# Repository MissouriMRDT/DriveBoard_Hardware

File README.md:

# DriveBoard_Hardware
Hardware files for Drive Board

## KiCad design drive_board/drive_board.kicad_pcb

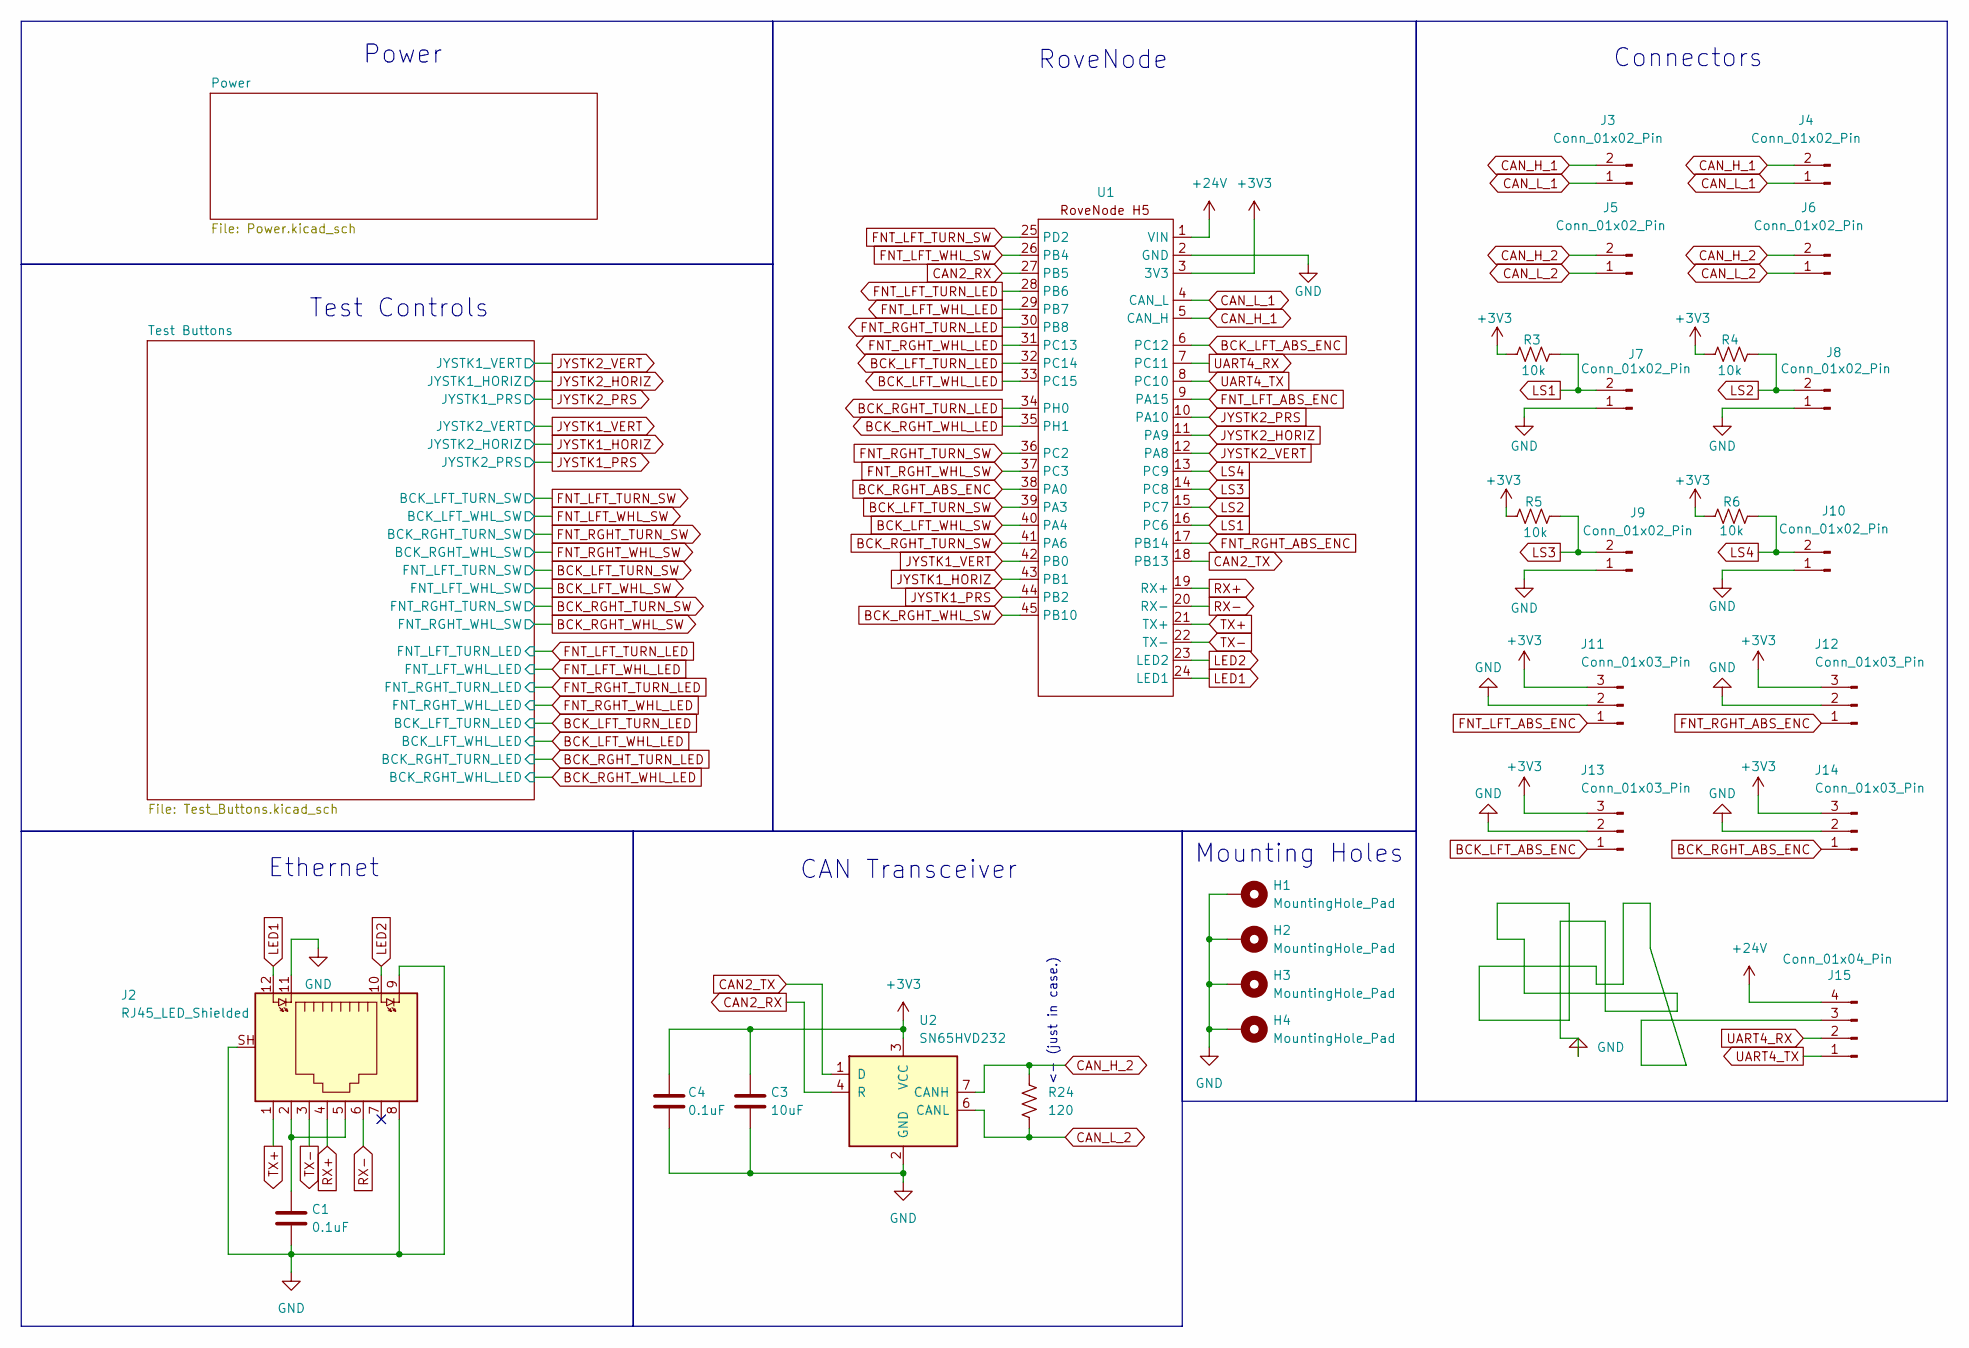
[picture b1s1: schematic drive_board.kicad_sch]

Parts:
C1, C4: 0.1uF; C_0603_1608Metric_Pad1.08x0.95mm_HandSolder
C3: 10uF; C_0603_1608Metric_Pad1.08x0.95mm_HandSolder
H1, H2, H3, H4: MountingHole_Pad; 4_40_Hole_Pad_Via
J2: RJ45_LED_Shielded; RJ45_Teensy
J3, J4, J5, J6, J7, J8, J9, J10: Conn_01x02_Pin; JST_PH_B2B-PH-K_1x02_P2.00mm_Vertical
J11, J12, J13, J14: Conn_01x03_Pin; JST_PH_B3B-PH-K_1x03_P2.00mm_Vertical
J15: Conn_01x04_Pin; JST_PH_B4B-PH-K_1x04_P2.00mm_Vertical
R3, R4, R5, R6: 10k; R_0603_1608Metric_Pad0.98x0.95mm_HandSolder
R24: 120; R_0603_1608Metric_Pad0.98x0.95mm_HandSolder
U1: RoveNode_H5
U2: SN65HVD232; SOIC-8_3.9x4.9mm_P1.27mm

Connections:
+3V3: C3.1, C4.1, J11.3, J12.3, J13.3, J14.3, R3.1, R4.1, R5.1, R6.1, U1.3 (3V3), U2.3 (VCC); also elsewhere on the board
+24V: J15.4, U1.1 (VIN); also elsewhere on the board
BCK_LFT_ABS_ENC: J13.1, U1.6 (PC12)
BCK_LFT_TURN_LED: U1.32 (PC14); also elsewhere on the board
BCK_LFT_TURN_SW: U1.39 (PA3); also elsewhere on the board
BCK_LFT_WHL_LED: U1.33 (PC15); also elsewhere on the board
BCK_LFT_WHL_SW: U1.40 (PA4); also elsewhere on the board
BCK_RGHT_ABS_ENC: J14.1, U1.38 (PA0)
BCK_RGHT_TURN_LED: U1.34 (PH0); also elsewhere on the board
BCK_RGHT_TURN_SW: U1.41 (PA6); also elsewhere on the board
BCK_RGHT_WHL_LED: U1.35 (PH1); also elsewhere on the board
BCK_RGHT_WHL_SW: U1.45 (PB10); also elsewhere on the board
CAN2_RX: U1.27 (PB5), U2.4 (R)
CAN2_TX: U1.18 (PB13), U2.1 (D)
CAN_H_1: J3.2, J4.2, U1.5 (CAN_H)
CAN_H_2: J5.2, J6.2, R24.1, U2.7 (CANH)
CAN_L_1: J3.1, J4.1, U1.4 (CAN_L)
CAN_L_2: J5.1, J6.1, R24.2, U2.6 (CANL)
FNT_LFT_ABS_ENC: J11.1, U1.9 (PA15)
FNT_LFT_TURN_LED: U1.28 (PB6); also elsewhere on the board
FNT_LFT_TURN_SW: U1.25 (PD2); also elsewhere on the board
FNT_LFT_WHL_LED: U1.29 (PB7); also elsewhere on the board
FNT_LFT_WHL_SW: U1.26 (PB4); also elsewhere on the board
FNT_RGHT_ABS_ENC: J12.1, U1.17 (PB14)
FNT_RGHT_TURN_LED: U1.30 (PB8); also elsewhere on the board
FNT_RGHT_TURN_SW: U1.36 (PC2); also elsewhere on the board
FNT_RGHT_WHL_LED: U1.31 (PC13); also elsewhere on the board
FNT_RGHT_WHL_SW: U1.37 (PC3); also elsewhere on the board
GND: C1.2, C3.2, C4.2, H1.1 (1_1), H2.1 (1_1), H3.1 (1_1), H4.1 (1_1), J2.8, J2.9, J2.11, J2.SH, J7.1, J8.1, J9.1, J10.1, J11.2, J12.2, J13.2, J14.2, J15.3, U1.2 (GND), U2.2 (GND); also elsewhere on the board
JYSTK1_HORIZ: U1.43 (PB1); also elsewhere on the board
JYSTK1_PRS: U1.44 (PB2); also elsewhere on the board
JYSTK1_VERT: U1.42 (PB0); also elsewhere on the board
JYSTK2_HORIZ: U1.11 (PA9); also elsewhere on the board
JYSTK2_PRS: U1.10 (PA10); also elsewhere on the board
JYSTK2_VERT: U1.12 (PA8); also elsewhere on the board
LED1: J2.12, U1.24 (LED1)
LED2: J2.10, U1.23 (LED2)
LS1: J7.2, R3.2, U1.16 (PC6)
LS2: J8.2, R4.2, U1.15 (PC7)
LS3: J9.2, R5.2, U1.14 (PC8)
LS4: J10.2, R6.2, U1.13 (PC9)
unnamed: C1.1, J2.2, J2.5
RX+: J2.4, U1.19 (RX+)
RX-: J2.6, U1.20 (RX-)
TX+: J2.1, U1.21 (TX+)
TX-: J2.3, U1.22 (TX-)
UART4_RX: J15.2, U1.7 (PC11)
UART4_TX: J15.1, U1.8 (PC10)

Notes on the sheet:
Power
Test Controls
Ethernet
Connectors
CAN Transceiver
<- (just in case.)
RoveNode
Mounting Holes

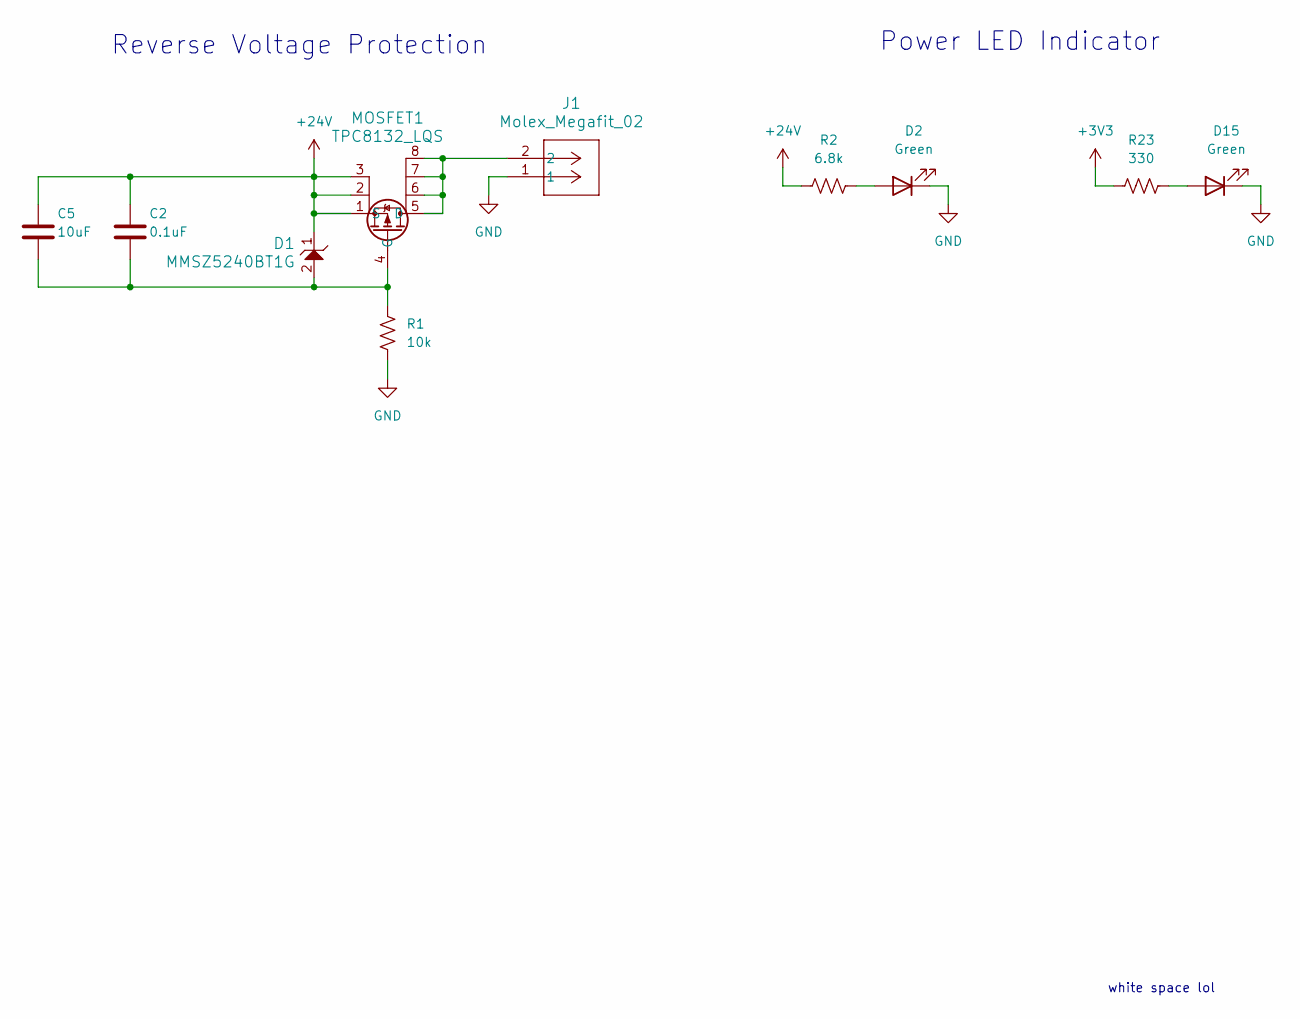
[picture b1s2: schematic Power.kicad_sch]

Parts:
C2: 0.1uF; C_0603_1608Metric_Pad1.08x0.95mm_HandSolder
C5: 10uF; C_0603_1608Metric_Pad1.08x0.95mm_HandSolder
D1: MMSZ5240BT1G; SOD-123_ONS-L
D2, D15: Green; LED_0603_1608Metric_Pad1.05x0.95mm_HandSolder
J1: Molex_Megafit_02; MOLEX_MegaFit_02_Vertical
MOSFET1: TPC8132_LQS; SOIC-8_3.9x4.9mm_P1.27mm
R1: 10k; R_0603_1608Metric_Pad0.98x0.95mm_HandSolder
R2: 6.8k; R_0603_1608Metric_Pad0.98x0.95mm_HandSolder
R23: 330; R_0603_1608Metric_Pad0.98x0.95mm_HandSolder

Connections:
+3V3: R23.1; also elsewhere on the board
+24V: C2.1, C5.1, D1.1, MOSFET1.1 (S), MOSFET1.2, MOSFET1.3, R2.1; also elsewhere on the board
GND: D2.1 (K), D15.1 (K), J1.1, R1.2; also elsewhere on the board
unnamed: D2.2 (A), R2.2
unnamed: D15.2 (A), R23.2
unnamed: J1.2, MOSFET1.5 (D), MOSFET1.6, MOSFET1.7, MOSFET1.8
unnamed: C2.2, C5.2, D1.2, MOSFET1.4 (G), R1.1

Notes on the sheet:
white space lol
Reverse Voltage Protection
Power LED Indicator

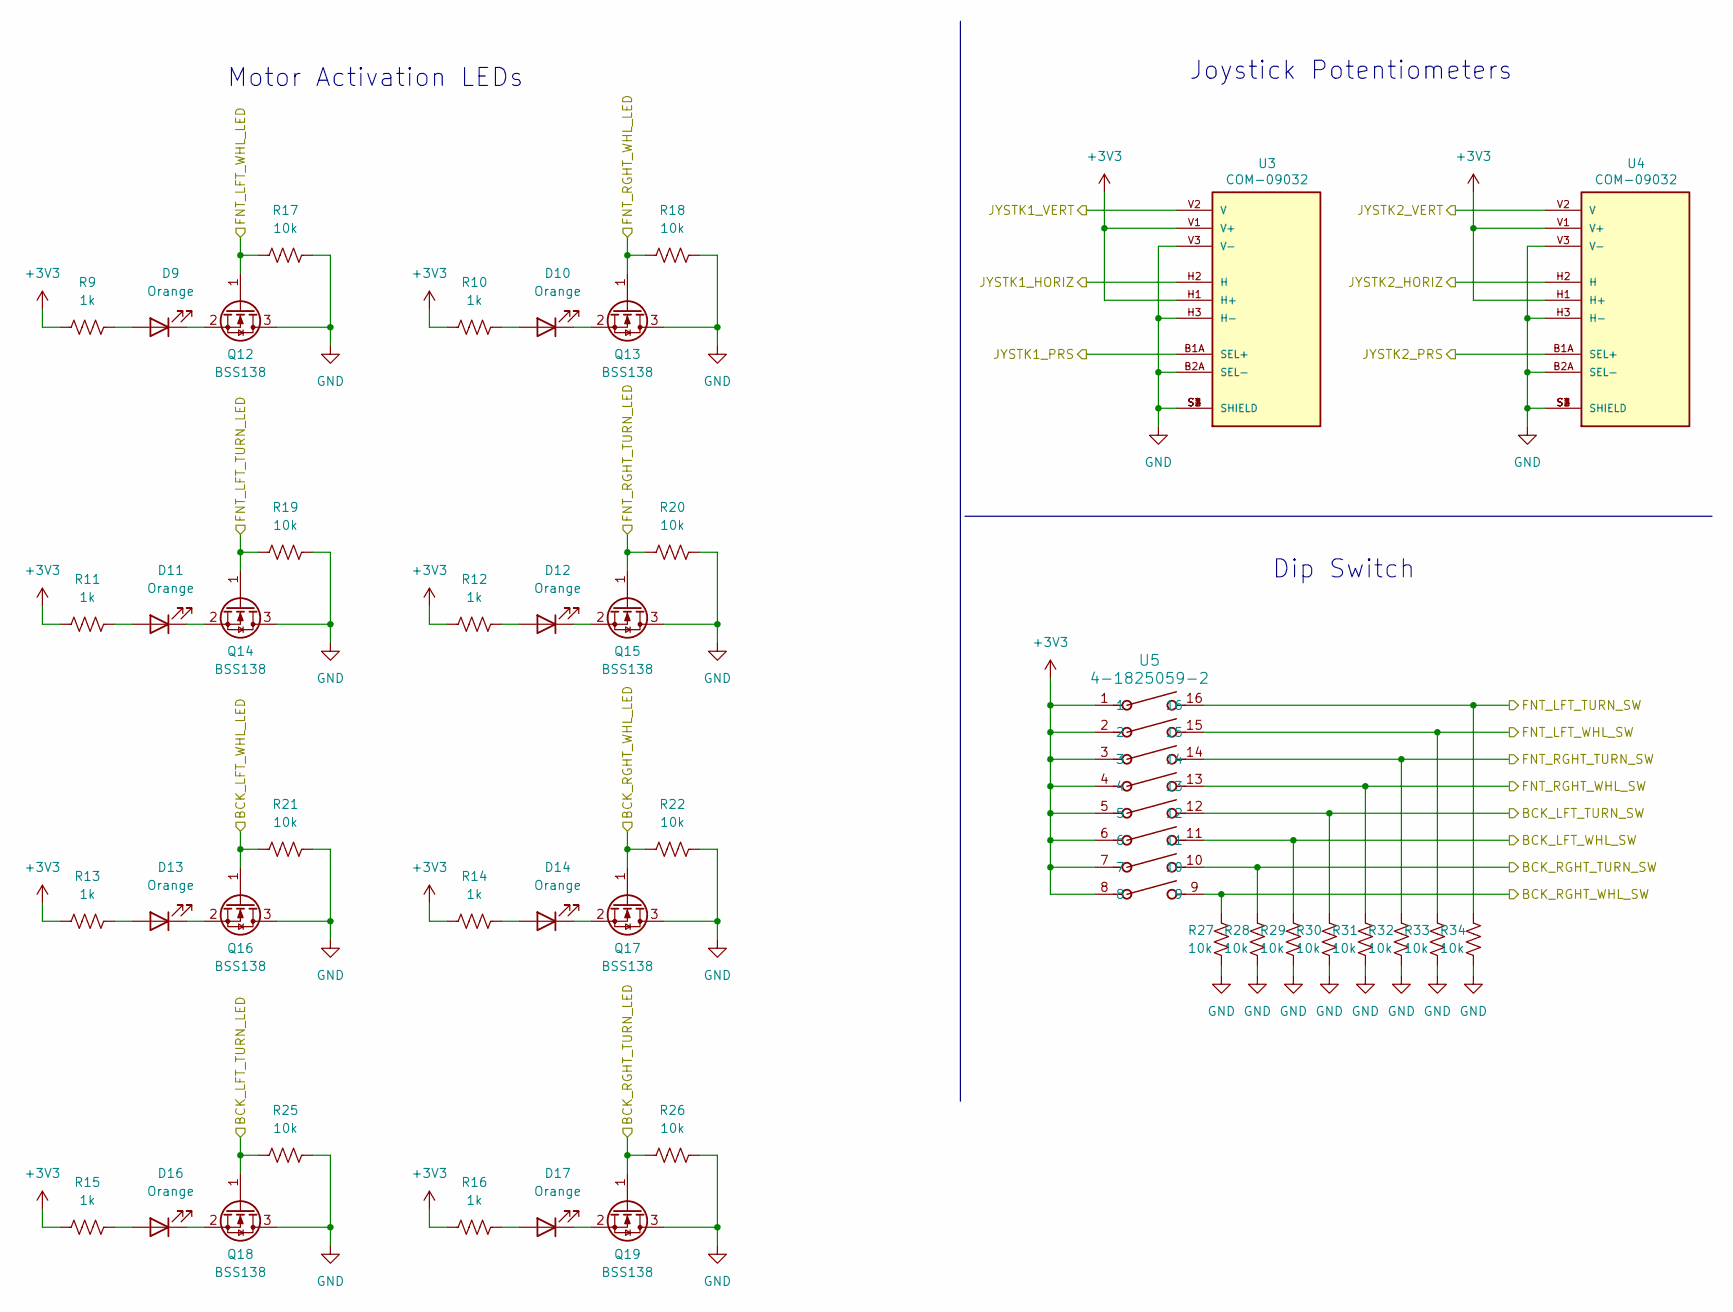
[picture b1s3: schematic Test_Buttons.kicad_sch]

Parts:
D9, D10, D11, D12, D13, D14, D16, D17: Orange; LED_0603_1608Metric_Pad1.05x0.95mm_HandSolder
Q12, Q13, Q14, Q15, Q16, Q17, Q18, Q19: BSS138; SOT-23
R9, R10, R11, R12, R13, R14, R15, R16: 1k; R_0603_1608Metric_Pad0.98x0.95mm_HandSolder
R17, R18, R19, R20, R21, R22, R25, R26, R27, R28, R29, R30, R31, R32, R33, R34: 10k; R_0603_1608Metric_Pad0.98x0.95mm_HandSolder
U3, U4: COM-09032; Joystick; PARTREV N/A
U5: 4-1825059-2; SW_DS04-254-1L-08BK

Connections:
+3V3: R9.1, R10.1, R11.1, R12.1, R13.1, R14.1, R15.1, R16.1, U3.H1 (H+), U3.V1 (V+), U4.H1 (H+), U4.V1 (V+), U5.1, U5.2, U5.3, U5.4, U5.5, U5.6, U5.7, U5.8; also elsewhere on the board
BCK_LFT_TURN_LED: Q18.1 (G), R25.1; also elsewhere on the board
BCK_LFT_TURN_SW: R34.2, U5.16; also elsewhere on the board
BCK_LFT_WHL_LED: Q16.1 (G), R21.1; also elsewhere on the board
BCK_LFT_WHL_SW: R33.2, U5.15; also elsewhere on the board
BCK_RGHT_TURN_LED: Q19.1 (G), R26.1; also elsewhere on the board
BCK_RGHT_TURN_SW: R32.2, U5.14; also elsewhere on the board
BCK_RGHT_WHL_LED: Q17.1 (G), R22.1; also elsewhere on the board
BCK_RGHT_WHL_SW: R31.2, U5.13; also elsewhere on the board
FNT_LFT_TURN_LED: Q14.1 (G), R19.1; also elsewhere on the board
FNT_LFT_TURN_SW: R30.2, U5.12; also elsewhere on the board
FNT_LFT_WHL_LED: Q12.1 (G), R17.1; also elsewhere on the board
FNT_LFT_WHL_SW: R29.2, U5.11; also elsewhere on the board
FNT_RGHT_TURN_LED: Q15.1 (G), R20.1; also elsewhere on the board
FNT_RGHT_TURN_SW: R28.2, U5.10; also elsewhere on the board
FNT_RGHT_WHL_LED: Q13.1 (G), R18.1; also elsewhere on the board
FNT_RGHT_WHL_SW: R27.2, U5.9; also elsewhere on the board
GND: Q12.3 (D), Q13.3 (D), Q14.3 (D), Q15.3 (D), Q16.3 (D), Q17.3 (D), Q18.3 (D), Q19.3 (D), R17.2, R18.2, R19.2, R20.2, R21.2, R22.2, R25.2, R26.2, R27.1, R28.1, R29.1, R30.1, R31.1, R32.1, R33.1, R34.1, U3.B2A (SEL-), U3.H3 (H-), U3.S1 (SHIELD), U3.S2 (SHIELD), U3.S3 (SHIELD), U3.S4 (SHIELD), U3.V3 (V-), U4.B2A (SEL-), U4.H3 (H-), U4.S1 (SHIELD), U4.S2 (SHIELD), U4.S3 (SHIELD), U4.S4 (SHIELD), U4.V3 (V-); also elsewhere on the board
JYSTK1_HORIZ: U4.H2 (H); also elsewhere on the board
JYSTK1_PRS: U4.B1A (SEL+); also elsewhere on the board
JYSTK1_VERT: U4.V2 (V); also elsewhere on the board
JYSTK2_HORIZ: U3.H2 (H); also elsewhere on the board
JYSTK2_PRS: U3.B1A (SEL+); also elsewhere on the board
JYSTK2_VERT: U3.V2 (V); also elsewhere on the board
unnamed: D9.2 (A), R9.2
unnamed: D9.1 (K), Q12.2 (S)
unnamed: D10.2 (A), R10.2
unnamed: D10.1 (K), Q13.2 (S)
unnamed: D11.2 (A), R11.2
unnamed: D11.1 (K), Q14.2 (S)
unnamed: D12.2 (A), R12.2
unnamed: D12.1 (K), Q15.2 (S)
unnamed: D13.2 (A), R13.2
unnamed: D13.1 (K), Q16.2 (S)
unnamed: D14.2 (A), R14.2
unnamed: D14.1 (K), Q17.2 (S)
unnamed: D16.2 (A), R15.2
unnamed: D16.1 (K), Q18.2 (S)
unnamed: D17.2 (A), R16.2
unnamed: D17.1 (K), Q19.2 (S)

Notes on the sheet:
Dip Switch
Joystick Potentiometers
Motor Activation LEDs

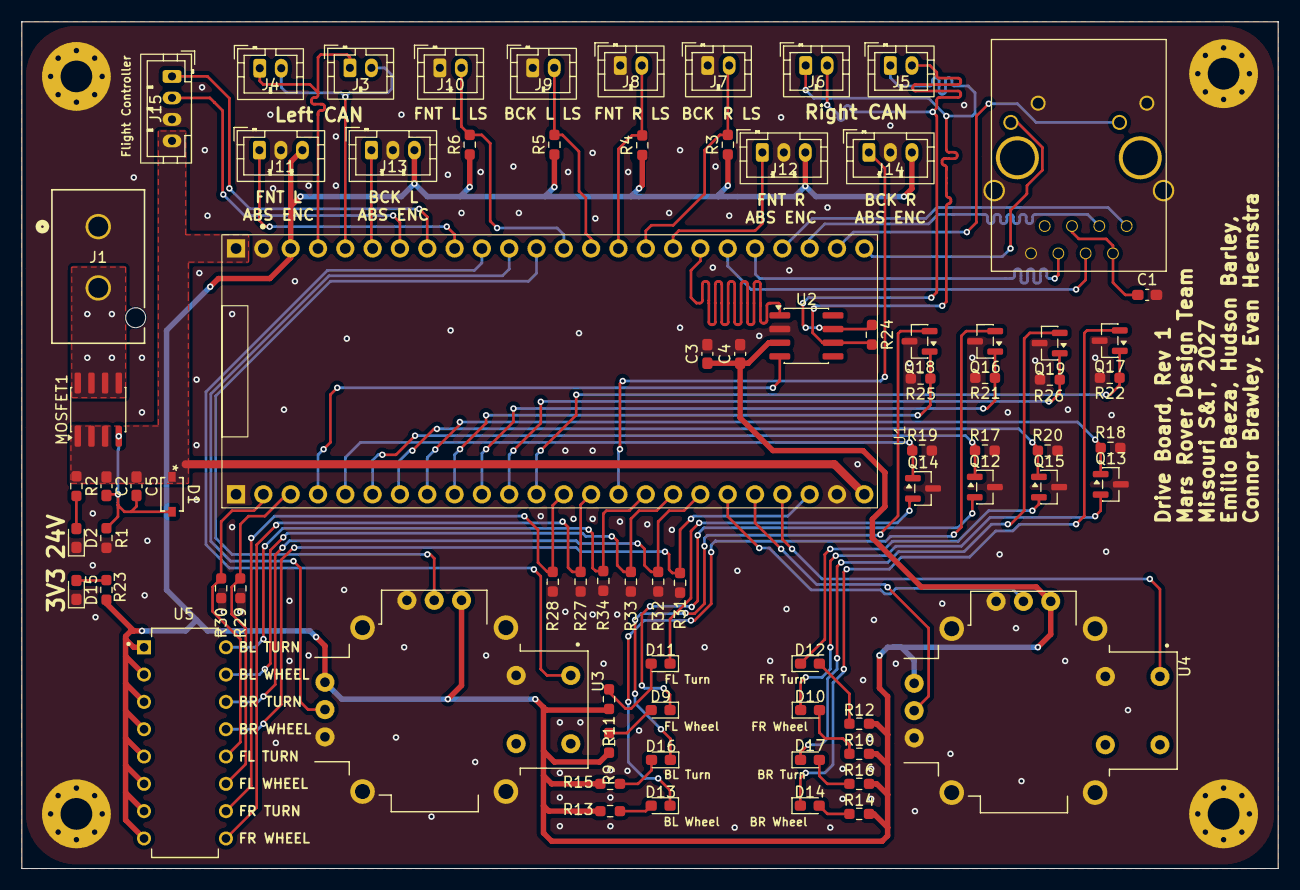
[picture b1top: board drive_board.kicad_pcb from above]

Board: 4 copper layers, 116.8 x 78.7 mm, 81 parts (0 on the bottom side), 68 nets.

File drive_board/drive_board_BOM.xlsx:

Designator | Package | Value | Item Name | Manufacturer Number | Part Number | Vendor | Quantity | Cost Per Item | Cost | URL
C1,C2,C4 | Capacitor_SMD:C_0603_1608Metric_Pad1.08x0.95mm_HandSolder | 0.1uF | Capacitor | CL10B104KB8NNNL | 1276-CL10B104KB8NNNLCT-ND | Digikey | 3 | 2.1600000000000001E-2 | 6.4799999999999996E-2 | https://www.digikey.com/en/products/detail/samsung-electro-m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
C3,C5 | Capacitor_SMD:C_0603_1608Metric_Pad1.08x0.95mm_HandSolder | 10uF | Capacitor | GRM188R6YA106MA73D | 490-13248-1-ND | Digikey | 2 | 4.5600000000000002E-2 | 9.1200000000000003E-2 | https://www.digikey.com/en/products/detail/murata-electronic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
D1 | MRDT_Devices:SOD-123_ONS-L | MMSZ5240BT1G | Zener Diode | MMSZ5240BT1G | MMSZ5240BT1GOSCT-ND | Digikey | 1 | 0.13600000000000001 | 0.13600000000000001 | https://www.digikey.com/en/products/detail/onsemi/MMSZ5240BT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
D2,D15 | LED_SMD:LED_0603_1608Metric_Pad1.05x0.95mm_HandSolder | Green | LED | LTST-C191KGKT | 160-1446-1-ND | Digikey | 2 | 0.104 | 0.20799999999999999 | https://www.digikey.com/product-detail/en/lite-on-inc/LTST-C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
D9,D10,D11,D12,D13,D14,D16,D17 | LED_SMD:LED_0603_1608Metric_Pad1.05x0.95mm_HandSolder | Orange | LED | LTST-C191KFKT | 160-1445-1-ND | Digikey | 8 | 9.8000000000000004E-2 | 0.78400000000000003 | https://www.digikey.com/en/products/detail/liteon/LTST-C191K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
J1 | megafit:CONN_SD-768290002_02_MOL | Molex_Megafit_02 | Molex Mega-Fit | 768290002 | WM11975-ND | Digikey | 1 | 0.89700000000000002 | 0.89700000000000002 | https://www.digikey.com/en/products/detail/molex/0768290002/5639617
J2 | MRDT_Connectors:RJ45_Teensy | RJ45_LED_Shielded | Connector | ETHERNET_KIT | N/A | PJRC | 1 | 9.9499999999999993 | 9.9499999999999993 | https://www.pjrc.com/store/ethernet_kit.html
J3,J4,J5,J6,J7,J8,J9,J10 | Connector_JST:JST_PH_B2B-PH-K_1x02_P2.00mm_Vertical | Conn_01x02_Pin | JST Connector | B2B-PH-K-S | 455-1704-ND | Digikey | 8 | 0.1 | 0.8 | https://www.digikey.com/en/products/detail/jst-sales-america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
J11,J12,J13,J14 | Connector_JST:JST_PH_B3B-PH-K_1x03_P2.00mm_Vertical | Conn_01x03_Pin | JST Connector | B3B-PH-K-S | 455-1705-ND | Digikey | 4 | 0.13600000000000001 | 0.54400000000000004 | https://www.digikey.com/en/products/detail/jst-sales-america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
J15 | Connector_JST:JST_PH_B4B-PH-K_1x04_P2.00mm_Vertical | Conn_01x04_Pin | JST Connector | B4B-PH-K-S | 455-1706-ND | Digikey | 1 | 0.16600000000000001 | 0.16600000000000001 | https://www.digikey.com/en/products/detail/jst-sales-america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
MOSFET1 | Package_SO:SOIC-8_3.9x4.9mm_P1.27mm | TPC8132_LQS | Mosfet | TPC8132,LQ(S | 264-TPC8132LQ(SCT-ND | Digikey | 1 | 1.04 | 1.04 | https://www.digikey.com/en/products/detail/toshiba-semicondu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
Q12,Q13,Q14,Q15,Q16,Q17,Q18,Q19 | Package_TO_SOT_SMD:SOT-23 | BSS138BK | Mosfet | BSS138BK,215 | 1727-1141-2-ND | Digikey | 8 | 0.20300000000000001 | 1.6240000000000001 | https://www.digikey.com/en/products/detail/nexperia-usa-inc/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
R1,R17,R18,R19,R20,R21,R22,R25,R26,R27,R28,R29,R30,R31,R32,R33,R34 | Resistor_SMD:R_0603_1608Metric_Pad0.98x0.95mm_HandSolder | 10k | Resistor | ESR03EZPF1002 | RHM10KADCT-ND | Digikey | 17 | 7.9000000000000001E-2 | 1.343 | https://www.digikey.com/en/products/detail/rohm-semiconducto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
R2 | Resistor_SMD:R_0603_1608Metric_Pad0.98x0.95mm_HandSolder | 6.8k | Resistor | RT0603BRD076K8L | YAG1724CT-ND | Digikey | 1 | 0.11 | 0.11 | https://www.digikey.com/en/products/detail/yageo/RT0603BRD07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
R9,R10,R11,R12,R13,R14,R15,R16 | Resistor_SMD:R_0603_1608Metric_Pad0.98x0.95mm_HandSolder | 1k | Resistor | ESR03EZPJ102 | RHM1.0KDCT-ND | Digikey | 8 | 0.11 | 0.88 | https://www.digikey.com/en/products/detail/rohm-semiconducto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
R23 | Resistor_SMD:R_0603_1608Metric_Pad0.98x0.95mm_HandSolder | 330 | Resistor | RC0603JR-07330RL | 311-330GRTR-ND | Digikey | 1 | 2.4E-2 | 2.4E-2 | https://www.digikey.com/en/products/detail/yageo/RC0603JR-07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
R24 | Resistor_SMD:R_0603_1608Metric_Pad0.98x0.95mm_HandSolder | 120 | Resistor | CRCW0603120RFKEAC | 541-CRCW0603120RFKEACCT-ND | Digikey | 1 | 0.1 | 0.1 | https://www.digikey.com/en/products/detail/vishay-dale/CRCW0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
U1 | MRDT_Shields:RoveNode_H5 |  | RoveNode | N/A | N/A | In-house | 1 | 25 | 25
U2 | Package_SO:SOIC-8_3.9x4.9mm_P1.27mm | SN65HVD232 | CAN Transceiver | SN65HVD232DR | 296-26344-1-ND | DigiKey | 1 | 2.91 | 2.91 | https://www.digikey.com/en/products/detail/texas-instruments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
U3,U4 | Joystick:XDCR_COM-09032 | COM-09032 | Analog Joystick | N/A | N/A | Amazon | 2 | 4.25 | 8.5 | https://www.amazon.com/TOMSIN-Joysticks-Replacement-Controll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
U5 | Dipswitch:SW_DS04-254-1L-08BK | 4-1825059-2 | Dip Switch | DS04-254-1L-08BK | 2223-DS04-254-1L-08BK-ND | Digikey | 1 | 2.12 | 2.12 | https://www.digikey.com/en/products/detail/te-connectivity-a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
PCB |  |  |  |  |  |  | 1 | 3 | 3
 |  |  |  |  |  |  |  | Total Cost | 60.291999999999994
